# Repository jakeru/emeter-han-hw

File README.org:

#+TITLE: Use HAN port to get electricity usage

This is a software engineer playing with KiCad.

I have tried a few approaches but the one that is now active is the
e-meter-han-usb-c variant. It consists of a ESP32 and a USB-C connector as well
as a connector for the HAN port.

Note that this is still work in progress!

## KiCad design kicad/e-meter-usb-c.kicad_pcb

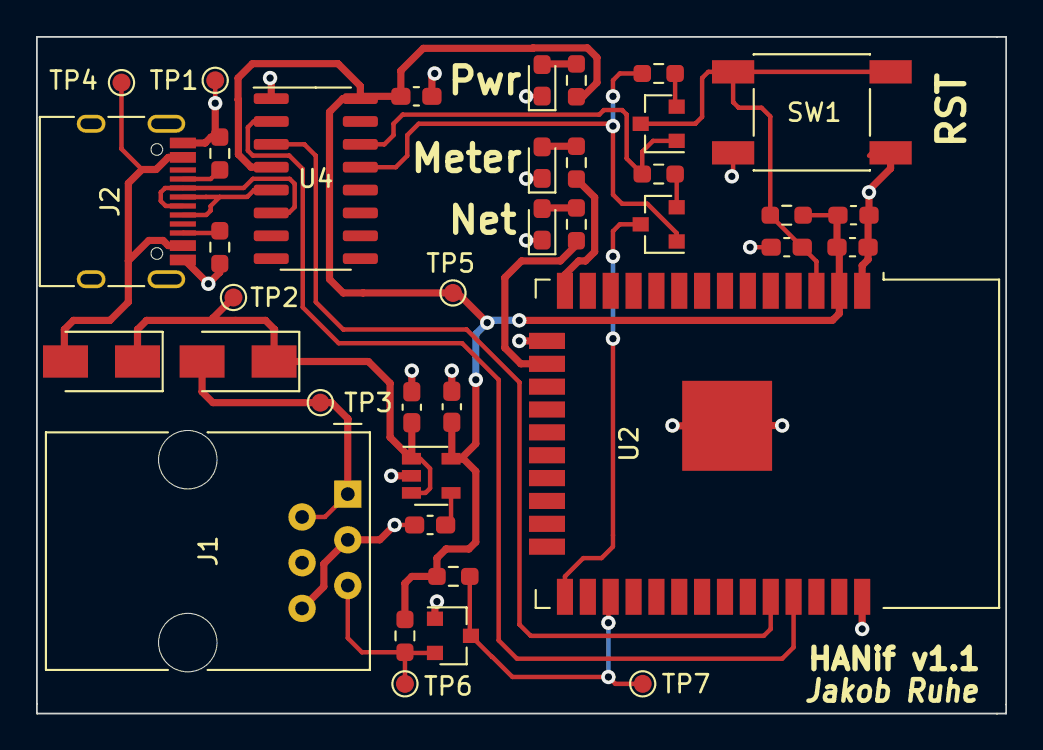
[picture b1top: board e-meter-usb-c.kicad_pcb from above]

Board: 2 copper layers, 53.8 x 37.6 mm, 38 parts (0 on the bottom side), 25 nets.

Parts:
C1: 10u; C_0603_1608Metric_Pad1.08x0.95mm_HandSolder
C2: 470p; C_0603_1608Metric_Pad1.08x0.95mm_HandSolder
C3: 2.2u; C_0603_1608Metric_Pad1.08x0.95mm_HandSolder
C4, C6, C7: 0.1u; C_0603_1608Metric_Pad1.08x0.95mm_HandSolder
C5: 22u; C_0603_1608Metric_Pad1.08x0.95mm_HandSolder
D1, D2: MDD-SS14; D_SMA
D3, D4, D5: LED; LED_0603_1608Metric_Pad1.05x0.95mm_HandSolder
J1: 6P6C; RJ12_Amphenol_54601
J2: USB_C_Receptacle_USB2.0; USB_C_Receptacle_HRO_TYPE-C-31-M-12
Q1, Q3, Q4: S8050; SOT-23
R2: 4.7k; R_0603_1608Metric_Pad0.98x0.95mm_HandSolder
R3, R7, R11: 68; R_0603_1608Metric_Pad0.98x0.95mm_HandSolder
R4, R5, R6, R10: 10k; R_0603_1608Metric_Pad0.98x0.95mm_HandSolder
R8, R9: 5.6k; R_0603_1608Metric_Pad0.98x0.95mm_HandSolder
SW1: SW_Push; TE_Connectivity_FSM2JSMAA
TP1, TP2, TP3, TP4, TP5, TP6, TP7: TestPoint; TestPoint_Pad_D1.0mm
U1: MIC5219-3.3YM5; SOT-23-5
U2: ESP32-WROOM-32
U4: CH340B (or C); SOIC-16_3.9x9.9mm_P1.27mm

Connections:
+3V3: C3.1, C4.1, C5.1, C6.2, R2.1, R3.2, R4.2, R10.2, TP5.1, U1.5, U2.2, U4.4, U4.16
/ESP_EN: C7.1, Q3.3, R10.1, SW1.1, U2.3
/ESP_FROM_UART: U2.34, U4.3
/ESP_IO0: Q4.3, U2.25
/ESP_TO_UART: U2.35, U4.2
/HAN_DATA: J1.5, Q1.2, R2.2, TP6.1
/HAN_DATA_REQ: D1.2, J1.1, J1.2, TP3.1
/HAN_TO_ESP: Q1.3, R4.1, TP7.1, U2.27
/METER_LED: R7.2, U2.14
/NETWORK_LED: R11.2, U2.16
/UART_DTR: Q4.1, R5.2, U4.13
/UART_RTS: Q3.1, R6.2, U4.14
/USB_D+: J2.A6, J2.B6, U4.5
/USB_D-: J2.A7, J2.B7, U4.6
/USB_VBUS: D2.2, J2.A4, J2.A9, J2.B4, J2.B9, TP4.1
GND: C1.2, C2.2, C3.2, C4.2, C5.2, C6.1, C7.2, D3.1, D4.1, D5.1, J1.3, J1.6, J2.A1, J2.A12, J2.B1, J2.B12, Q1.1, R8.2, R9.2, SW1.2, TP1.1, U1.2, U2.1, U2.15, U2.38, U2.39, U4.1
unnamed: C2.1, U1.4
unnamed: D3.2, R3.1
unnamed: D4.2, R7.1
unnamed: D5.2, R11.1
unnamed: J2.A5, R8.1
unnamed: J2.B5, R9.1
unnamed: Q3.2, R5.1
unnamed: Q4.2, R6.1
VCC: C1.1, D1.1, D2.1, TP2.1, U1.1, U1.3

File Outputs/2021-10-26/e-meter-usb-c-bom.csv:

Comment,Designator,Footprint,LCSC Part #
10u Unpolarized capacitor,C1,C_0603_1608Metric_Pad1.08x0.95mm_HandSolder,
470p Unpolarized capacitor,C2,C_0603_1608Metric_Pad1.08x0.95mm_HandSolder,
2.2u Unpolarized capacitor,C3,C_0603_1608Metric_Pad1.08x0.95mm_HandSolder,
0.1u Unpolarized capacitor,"C4,C6,C7",C_0603_1608Metric_Pad1.08x0.95mm_HandSolder,
22u Unpolarized capacitor,C5,C_0603_1608Metric_Pad1.08x0.95mm_HandSolder,
"MDD-SS14 40V 1A Schottky Barrier Rectifier Diode, SMA(DO-214AC)","D1,D2",D_SMA,C2480
LED Light emitting diode,"D3,D4,D5",LED_0201_0603Metric_Pad0.64x0.40mm_HandSolder,C2290
"6P6C RJ connector, 6P6C (6 positions 6 connected), RJ12/RJ18/RJ25",J1,RJ12_Amphenol_54601,C305981
USB_C_Receptacle_USB2.0 USB 2.0-only Type-C Receptacle connector,J2,USB_C_Receptacle_HRO_TYPE-C-31-M-12,C165948
"S8050 0.7A Ic, 20V Vce, Low Voltage High Current NPN Transistor, TO-92","Q1,Q3,Q4",SOT-23,C2150
"4.7k Resistor, US symbol",R2,R_0201_0603Metric_Pad0.64x0.40mm_HandSolder,
"60 Resistor, US symbol","R3,R7,R11",R_0201_0603Metric_Pad0.64x0.40mm_HandSolder,
"10k Resistor, US symbol","R4,R5,R6,R10",R_0201_0603Metric_Pad0.64x0.40mm_HandSolder,
"5.6k Resistor, US symbol","R8,R9",R_0201_0603Metric_Pad0.64x0.40mm_HandSolder,
"SW_Push Push button switch, generic, two pins",SW1,TE_Connectivity_FSM2JSMAA,C127509
"ESP32-WROOM-32 RF Module, ESP32-D0WDQ6 SoC, Wi-Fi 802.11b/g/n, Bluetooth, BLE, 32-bit, 2.7-3.6V, onboard antenna, SMD",U2,ESP32-WROOM-32,C82899
"CH340B (or C) USB serial converter, UART, SOIC-16",U4,SOIC-16_3.9x9.9mm_P1.27mm,C81010

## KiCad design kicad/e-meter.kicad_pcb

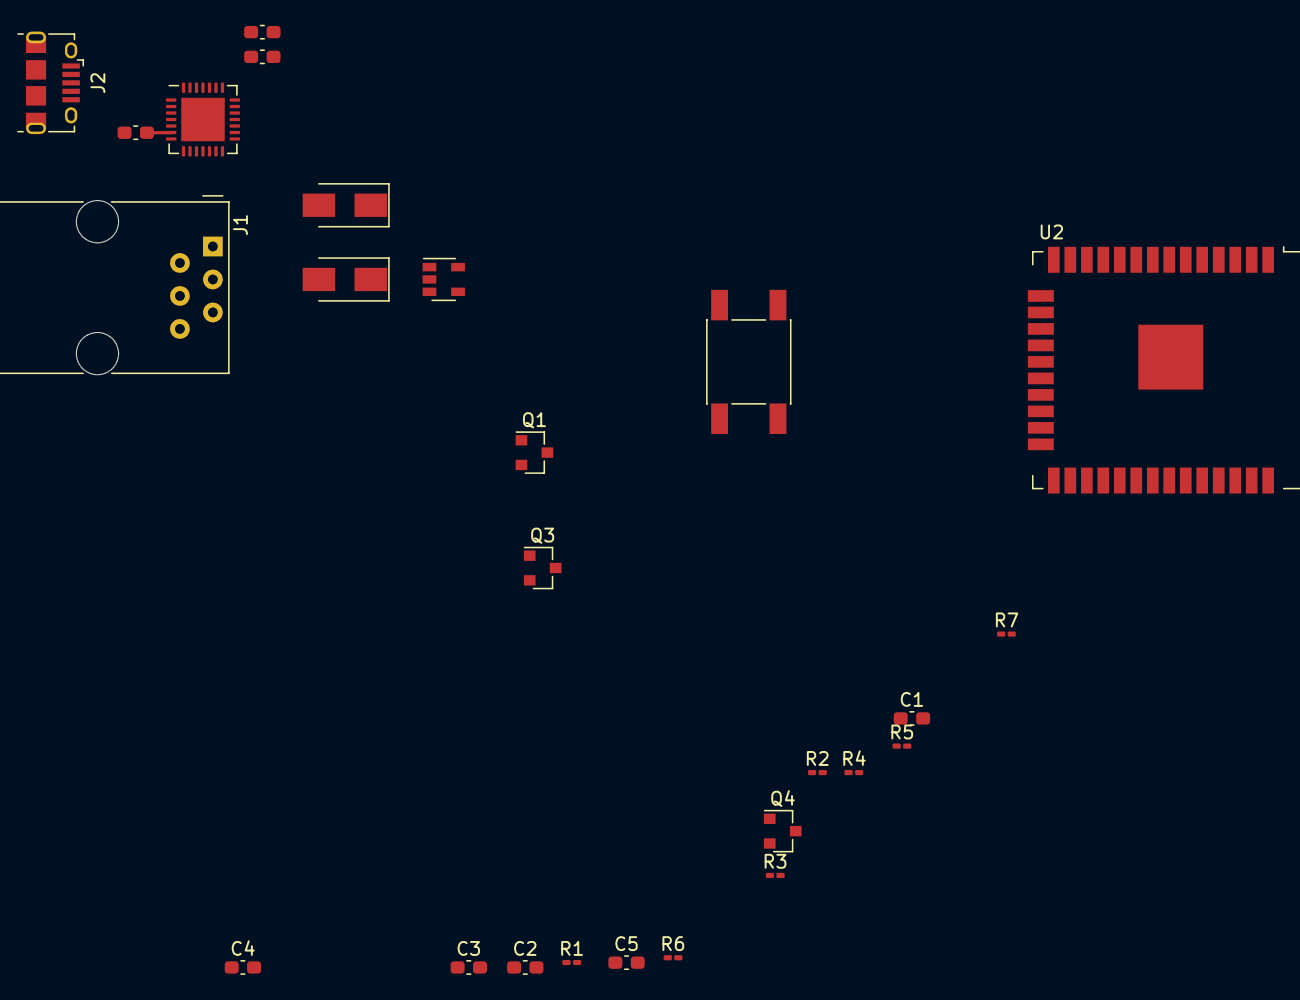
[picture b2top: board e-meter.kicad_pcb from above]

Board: 2 copper layers, 26 parts (0 on the bottom side), 20 nets.

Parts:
C1, C2: 10u; C_0603_1608Metric_Pad1.08x0.95mm_HandSolder
C3, C5, C6: 1u; C_0603_1608Metric_Pad1.08x0.95mm_HandSolder
C4: 22u; C_0603_1608Metric_Pad1.08x0.95mm_HandSolder
C7, C8: 0.1u; C_0603_1608Metric_Pad1.08x0.95mm_HandSolder
D1, D2: MDD-SS14; D_SMA
J1: 6P6C; RJ12_Amphenol_54601
J2: USB_B_Micro; USB_Micro-B_Amphenol_10118194_Horizontal
Q1, Q3, Q4: S8050; SOT-23
R1: 100K; R_0201_0603Metric_Pad0.64x0.40mm_HandSolder
R2, R3, R4: 1K; R_0201_0603Metric_Pad0.64x0.40mm_HandSolder
R5, R6: 10k; R_0201_0603Metric_Pad0.64x0.40mm_HandSolder
R7: 10K; R_0201_0603Metric_Pad0.64x0.40mm_HandSolder
SW1: SW_Push; TE_Connectivity_FSM2JSMAA
U1: AP2112K-3.3; SOT-23-5
U2: ESP32-WROOM-32
U3: CP2102N-A01-GQFN28; QFN-28-1EP_5x5mm_P0.5mm_EP3.35x3.35mm

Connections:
+3V3: C2.1, C3.1, C4.1, R2.1, R4.2, R7.1, U1.5, U2.2
/CP_DTR: Q4.1, R5.2, U3.28
/CP_REGIN: C6.1, C8.1, D2.2, J2.1, U3.7, U3.8
/CP_RTS: Q3.1, R6.2, U3.24
/CP_RXD: U2.35, U3.25
/CP_TXD: U2.34, U3.26
/CP_VDD: C7.2, U3.6
/EN: C5.1, Q3.3, R7.2, SW1.2, U2.3
/HAN_DATA: J1.5, Q1.2, R2.2
/HAN_DATA_REQ: J1.2, R3.1
/HAN_VCC: D1.2, J1.1, R3.2
/IO0: Q4.3, U2.25
/RX: Q1.3, R4.1
/USB_DM: J2.2, U3.5
/USB_DP: J2.3, U3.4
/VCC: C1.1, D1.1, D2.1, R1.2, U1.1
GND: C1.2, C2.2, C3.2, C4.2, C5.2, C6.2, C7.1, C8.2, J1.3, J1.6, J2.5, Q1.1, SW1.1, U1.2, U2.1, U2.15, U2.38, U2.39, U3.3, U3.29
unnamed: Q3.2, R5.1
unnamed: Q4.2, R6.1
unnamed: R1.1, U1.3

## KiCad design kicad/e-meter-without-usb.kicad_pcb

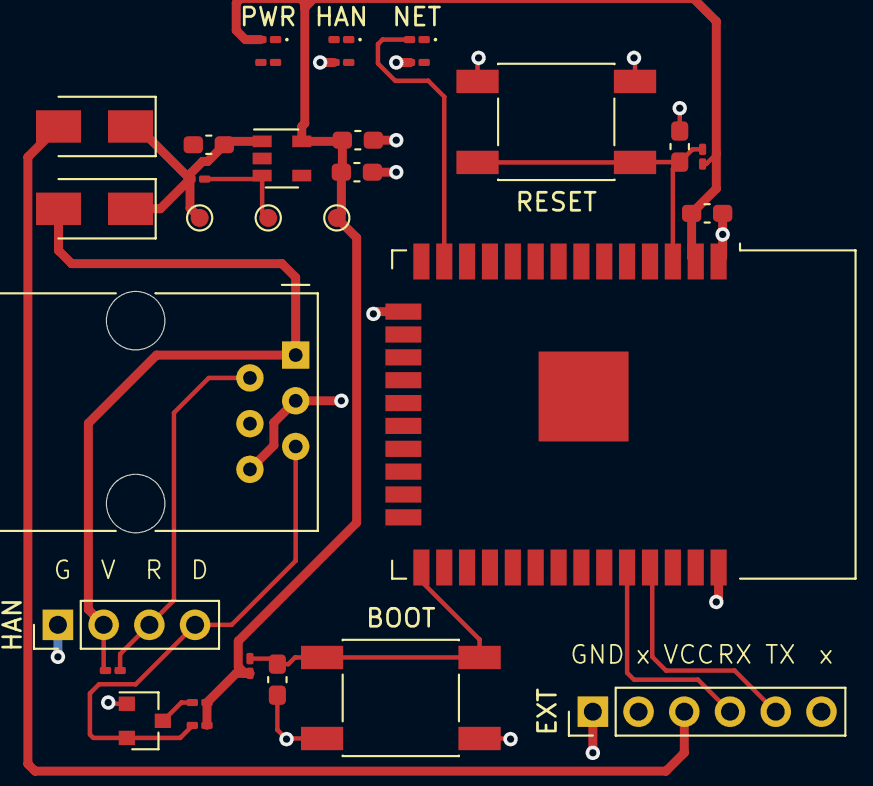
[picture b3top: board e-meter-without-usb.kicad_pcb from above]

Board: 2 copper layers, 31 parts (0 on the bottom side), 18 nets.

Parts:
BOOT: SW_Push; TE_Connectivity_FSM2JSMAA
C1, C2: 10u; C_0603_1608Metric_Pad1.08x0.95mm_HandSolder
C3, C5, C6: 1u; C_0603_1608Metric_Pad1.08x0.95mm_HandSolder
C4: 22u; C_0603_1608Metric_Pad1.08x0.95mm_HandSolder
D1, D2: MDD-SS14; D_SMA
EXT: Conn_01x06; PinHeader_1x06_P2.54mm_Vertical
HAN: LED; LED_0201_0603Metric_Pad0.64x0.40mm_HandSolder
HAN#2: Conn_01x04; PinHeader_1x04_P2.54mm_Vertical
J1: 6P6C; RJ12_Amphenol_54601
NET: LED; LED_0201_0603Metric_Pad0.64x0.40mm_HandSolder
PWR: LED; LED_0201_0603Metric_Pad0.64x0.40mm_HandSolder
Q1: S8050; SOT-23
R1: 100K; R_0201_0603Metric_Pad0.64x0.40mm_HandSolder
R2, R3, R4: 1K; R_0201_0603Metric_Pad0.64x0.40mm_HandSolder
R5, R6, R9: 2K; R_0201_0603Metric_Pad0.64x0.40mm_HandSolder
R7, R8: 10K; R_0201_0603Metric_Pad0.64x0.40mm_HandSolder
RESET: SW_Push; TE_Connectivity_FSM2JSMAA
TP1, TP2, TP3: TestPoint; TestPoint_Pad_D1.0mm
U1: AP2112K-3.3; SOT-23-5
U2: ESP32-WROOM-32

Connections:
+3V3: C2.1, C3.1, C4.1, PWR.2, R2.1, R4.2, R7.1, R8.1, TP3.1, U1.5, U2.2
/BOOT: BOOT.2, C6.1, R8.2, U2.25
/EN: C5.1, R7.2, RESET.2, U2.3
/EXT_5V: D1.2, EXT.3
/EXT_FROM_ESP: EXT.5, U2.35
/EXT_TO_ESP: EXT.4, U2.34
/HAN_DATA: HAN#2.4, J1.5, Q1.2, R2.2
/HAN_DATA_REQ: HAN#2.3, J1.2, R3.1
/HAN_VCC: D2.2, HAN#2.2, J1.1, R3.2
/METER_LED: HAN.2, U2.23
/NETWORK_LED: NET.2, U2.13
/RX: Q1.3, R4.1
/VCC: C1.1, D1.1, D2.1, R1.2, TP1.1, U1.1
GND: BOOT.1, C1.2, C2.2, C3.2, C4.2, C5.2, C6.2, EXT.1, HAN#2.1, J1.3, J1.6, Q1.1, R5.1, R6.1, R9.1, RESET.1, U1.2, U2.1, U2.15, U2.38, U2.39
unnamed: PWR.1, R5.2
unnamed: NET.1, R6.2
unnamed: HAN.1, R9.2
unnamed: R1.1, TP2.1, U1.3

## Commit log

2021-10-23 Initial commit (WIP)
2021-10-27 Change a few components
    I could not find the USB converter CH340C so went for CH340B instead.
    Same for the 3.3 Volt converter. I had to change it to another one, but
    even that one is not available at JLCPCB so I will have to solder it by
    hand.
2021-10-27 Add Output files 2021-10-26
    I never actually placed an order but I wanted to see the price of it and
    see if I remembered how to order things from JLCPCB.
    I noticed that a couple of components needs to be rotated and/or moved
    in order to be placed correctly.
    I should also add part numbers to the resistors and capacitors in order
    to have them mounted as well.
2021-10-27 Add a README file
2021-11-06 Small updates, first order
    This was ordered from JLCPCB late yesterday evening.
2021-11-06 Fix resistors, LEDs and text
    I used a too small footprint for resistors and LEDs for the first order.
    This fixes that and also puts more text in the silk layer.
